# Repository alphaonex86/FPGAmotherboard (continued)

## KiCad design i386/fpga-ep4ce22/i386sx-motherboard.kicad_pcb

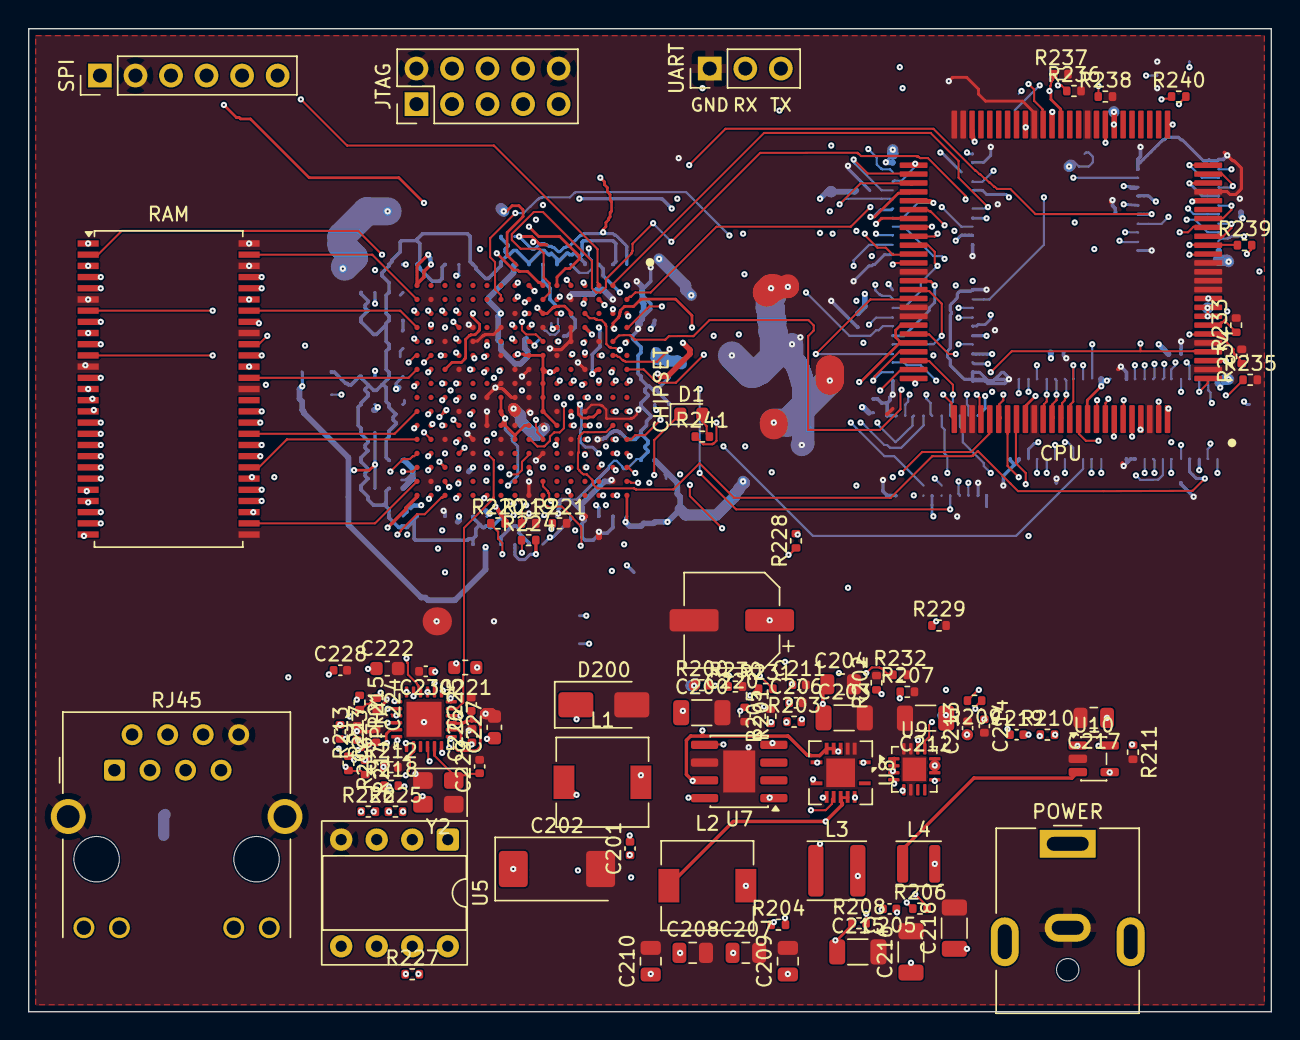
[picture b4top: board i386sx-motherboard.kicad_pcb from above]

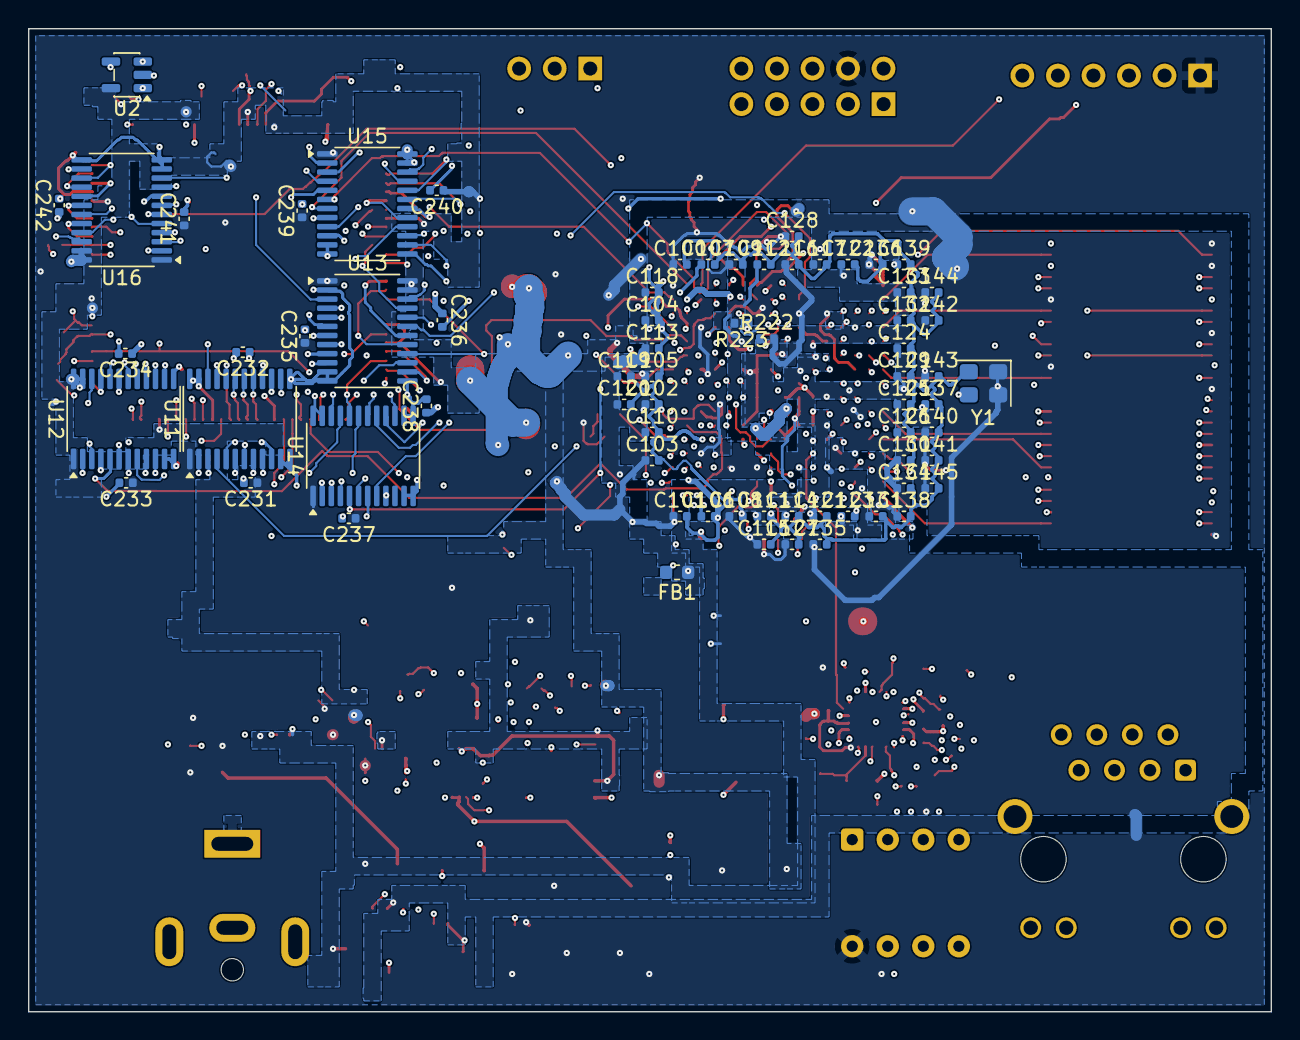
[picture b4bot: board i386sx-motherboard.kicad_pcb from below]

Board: 6 copper layers, 88.8 x 70.2 mm, 161 parts (69 on the bottom side), 213 nets.

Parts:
C100, C101, C102, C103, C104, C105, C106, C107, C108, C109, C110, C111, C112, C113, C114, C115, C116, C117, C118, C119, C120, C121, C122, C123, C124, C125, C126, C127, C128, C129, C130, C131, C132, C133, C134, C135, C136, C137, C138, C139, C140, C141, C142, C143, C144, C145: 100nF; C_0402_1005Metric
C200, C203, C212, C215, C216, C218: 22uF 25V X5R; C_1206_3216Metric
C201, C206: 10nF 50V X7R; C_0402_1005Metric
C202: 220uF 10V ESR<=40mR; CP_EIA-7343-31_Kemet-D
C204: 4.7uF 25V X7R; C_0805_2012Metric
C205, C213, C223, C224, C225, C228, C231, C232, C233, C234, C235, C236, C237, C238, C239, C240, C241, C242: 100nF 16V X7R; C_0402_1005Metric
C207, C208, C209, C210: 47uF 6.3V X5R; C_0805_2012Metric
C211: 8.2nF 50V X7R; C_0402_1005Metric
C214: 3.3nF 50V X7R; C_0402_1005Metric
C217: 10uF 16V X5R; C_0805_2012Metric
C219: 6.8pF 50V C0G; C_0402_1005Metric
C220: 100uF 25V; CP_Elec_6.3x7.7
C221: 600R@100MHz bead; L_0603_1608Metric
C222: 10uF 10V X5R; C_0603_1608Metric
C226: 470pF 50V C0G; C_0402_1005Metric
C227: 1uF 16V X7R; C_0603_1608Metric
C229, C230: 15pF 50V C0G; C_0402_1005Metric
D1: red LED KT-0603R; LED_0603_1608Metric
D200: B340A 40V 3A; D_SMA
FB1: 600R@100MHz bead; L_0603_1608Metric
J1: HR911105A; RJ45_Hanrun_HR911105A_Horizontal
J2: PJ-063AH 12V; BarrelJack_CUI_PJ-063AH_Horizontal
J3: JTAG; PinHeader_2x05_P2.54mm_Vertical
J4: SPI ISP; PinHeader_1x06_P2.54mm_Vertical
J5: UART; PinHeader_1x03_P2.54mm_Vertical
L1: 10uH ETQP4M100YFN; L_6.3x6.3_H3
L2: 2.2uH SRN6045TA-2R2Y; L_6.3x6.3_H3
L3: 2.2uH SLW4020P2R2MST; L_APV_ANR4020
L4: 1.0uH VLS3012HBX-1R0M; L_APV_ANR3012
R200: 30.9k 1%; R_0402_1005Metric
R201, R205, R207, R213, R222, R223, R224, R226, R227, R228, R229: 10k 1%; R_0402_1005Metric
R202, R208, R209, R211: 100k 1%; R_0402_1005Metric
R203: 1.69k 1%; R_0402_1005Metric
R204: 31.6k 1%; R_0402_1005Metric
R206: 4.99k 1%; R_0402_1005Metric
R210, R231: 316k 1%; R_0402_1005Metric
R212: 12.1k 1%; R_0402_1005Metric
R214, R215, R216, R217: 49.9 1%; R_0402_1005Metric
R218: 500R 1%; R_0402_1005Metric
R219, R220, R221: 0R; R_0402_1005Metric
R225: 24.9R 1%; R_0402_1005Metric
R230, R233, R234, R235, R236, R237, R238: 1k 1%; R_0402_1005Metric
R232: 46.4k 1%; R_0402_1005Metric
R239, R240: 21.5k 1%; R_0402_1005Metric
R241: 330R 1%; R_0402_1005Metric
U1: NG80386SX-20; Intel_PQFP-100_19.05x19.05mm_P0.635mm
U2: SN74AHCT1G125DBVR; SOT-23-5
U3: EP4CE22F17C8N; Altera_FBGA-256_F256_17x17mm_Layout16x16_P1.0mm
U4: W9825G6KH-6I; TSOP-II-54_22.2x10.16mm_P0.8mm
U5: W25Q64FVDAIG (DIP-8, socketed); DIP-8_W7.62mm_Socket
U6: LAN8720A-CP-TR; QFN-24-1EP_4x4mm_P0.5mm_EP2.5x2.5mm
U7: TPS5430DDAR 12->5V; SOIC-8-1EP_3.9x4.9mm_P1.27mm_EP2.29x3mm
U8: TPS54620RGYR 12->3V3; Texas_S-PVQFN-N14
U9: TPS62130RGTR VCCINT; VQFN-16-1EP_3x3mm_P0.5mm_EP1.68x1.68mm
U10: TLV62569DBVR VCCAUX; SOT-23-5
U11, U12, U13, U14, U15, U16: SN74LVC8T245PWR; TSSOP-24_4.4x7.8mm_P0.65mm
Y1: 25MHz XO; Oscillator_SMD_Abracon_ASE-4Pin_3.2x2.5mm
Y2: 25MHz; Crystal_SMD_3225-4Pin_3.2x2.5mm

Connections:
+3V3: C100.1, C101.1, C102.1, C103.1, C104.1, C105.1, C108.1, C109.1, C115.1, C116.1, C127.1, C128.1, C135.1, C136.1, C140.1, C141.1, C142.1, C143.1, C144.1, C145.1, C207.1, C208.1, C209.1, C210.1, C212.1, C213.1, C217.1, C221.1, C225.1, C231.1, C233.1, C235.1, C237.1, C239.1, C241.1, J3.4, J4.1, L2.2, R204.1, R209.1, R222.2, R223.2, R224.2, R226.2, R227.2, R228.2, R241.1, U3.A1 (VCCIO8), U3.A16 (VCCIO7), U3.C4 (VCCIO8), U3.C7 (VCCIO8), U3.C10 (VCCIO7), U3.C13 (VCCIO7), U3.E3 (VCCIO1), U3.E14 (VCCIO6), U3.G3 (VCCIO1), U3.G14 (VCCIO6), U3.K3 (VCCIO2), U3.K14 (VCCIO5), U3.M3 (VCCIO2), U3.M14 (VCCIO5), U3.P4 (VCCIO3), U3.P7 (VCCIO3), U3.P10 (VCCIO4), U3.P13 (VCCIO4), U3.T1 (VCCIO3), U3.T16 (VCCIO4), U4.1, U4.3, U4.9, U4.14, U4.27, U4.43, U4.49, U5.8, U6.9, U9.10, U9.11, U9.12, U10.1, U10.4, U11.1, U12.1, U13.1, U14.1, U15.1, U16.1, Y1.1, Y1.4
+5V: C202.1, C232.1, C234.1, C236.1, C238.1, C240.1, C242.1, L1.2, R200.1, R239.2, R240.2, U1.8, U1.9, U1.10, U1.21, U1.32, U1.39, U1.42, U1.48, U1.57, U1.69, U1.71, U1.84, U1.91, U1.97, U2.5, U11.23, U11.24, U12.23, U12.24, U13.23, U13.24, U14.23, U14.24, U15.23, U15.24, U16.23, U16.24
+12V: C200.1, C203.1, C204.1, C220.1, J2.1, R231.1, U7.7, U8.4, U8.5, U8.6
GND: C100.2, C101.2, C102.2, C103.2, C104.2, C105.2, C106.2, C107.2, C108.2, C109.2, C110.2, C111.2, C112.2, C113.2, C114.2, C115.2, C116.2, C117.2, C118.2, C119.2, C120.2, C121.2, C122.2, C123.2, C124.2, C125.2, C126.2, C127.2, C128.2, C129.2, C130.2, C131.2, C132.2, C133.2, C134.2, C135.2, C136.2, C137.2, C138.2, C139.2, C140.2, C141.2, C142.2, C143.2, C144.2, C145.2, C200.2, C202.2, C203.2, C204.2, C206.2, C207.2, C208.2, C209.2, C210.2, C211.2, C212.2, C213.2, C214.2, C215.2, C216.2, C217.2, C218.2, C220.2, C222.2, C223.2, C224.2, C225.2, C226.2, C227.2, C228.2, C229.2, C230.2, C231.2, C232.2, C233.2, C234.2, C235.2, C236.2, C237.2, C238.2, C239.2, C240.2, C241.2, C242.2, D200.2, J1.8, J1.SH, J2.2, J3.2, J3.10, J4.2, J5.1, R201.2, R202.2, R205.2, R207.2, R211.2, R212.2, R213.2, R219.2, R221.2, R229.2, R230.2, R232.2, R233.2, R234.2, R235.2, R236.2, R237.2, R238.2, U1.2, U1.5, U1.11, U1.12, U1.13, U1.14, U1.22, U1.35, U1.41, U1.49, U1.50, U1.63, U1.67, U1.68, U1.77, U1.78, U1.85, U1.98, U2.1, U2.3, U3.B2 (GND), U3.B15 (GND), U3.C5 (GND), U3.C12 (GND), U3.D7 (GND), U3.D10 (GND), U3.E2 (GND), U3.E4 (GND), U3.E5 (GNDA3), U3.E12 (GNDA2), U3.E13 (GND), U3.F6 (GND), U3.F10 (GND), U3.G4 (GND), U3.G11 (GND), U3.G13 (GND), U3.H7 (GND), U3.H8 (GND), U3.H9 (GND), U3.H10 (GND), U3.H15 (GND), U3.H16 (GND), U3.J3 (nCE), U3.J7 (GND), U3.J8 (GND), U3.J9 (GND), U3.J10 (GND), U3.J11 (GND), U3.K4 (GND), U3.K6 (GND), U3.K8 (GND), U3.K12 (GND), U3.K13 (GND), U3.L9 (GND), U3.L10 (GND), U3.L11 (GND), U3.M4 (GND), U3.M5 (GNDA1), U3.M12 (GNDA4), U3.M13 (GND), U3.N7 (GND), U3.N10 (GND), U3.P5 (GND), U3.P12 (GND), U3.R2 (GND), U3.R15 (GND), U4.6, U4.12, U4.28, U4.41, U4.46, U4.52, U4.54, U5.4, U6.25, U7.6, U7.9, U8.2, U8.3, U8.15, U9.6, U9.15, U9.16, U9.17, U10.2, U11.11, U11.12, U11.13, U12.11, U12.12, U12.13, U13.2, U13.11, U13.12, U13.13, U14.2, U14.11, U14.12, U14.13, U14.14, U15.2, U15.11, U15.12, U15.13, U16.2, U16.11, U16.12, U16.13, Y1.2, Y2.2, Y2.4
VCCA_PLL: C111.1, C112.1, C131.1, C132.1, C218.1, C219.1, L4.2, R210.1, R220.2, U3.F5 (VCCA3), U3.F12 (VCCA2), U3.L5 (VCCA1), U3.L12 (VCCA4)
VCCD_PLL: C106.1, C107.1, C138.1, C139.1, FB1.2, U3.D4 (VCCD_PLL3), U3.D13 (VCCD_PLL2), U3.N4 (VCCD_PLL1), U3.N13 (VCCD_PLL4)
VCCINT: C110.1, C113.1, C114.1, C117.1, C118.1, C119.1, C120.1, C121.1, C122.1, C123.1, C124.1, C125.1, C126.1, C129.1, C130.1, C133.1, C134.1, C137.1, C215.1, C216.1, FB1.1, L3.2, R206.1, R208.1, U3.F7 (VCCINT), U3.F11 (VCCINT), U3.G6 (VCCINT), U3.G7 (VCCINT), U3.G8 (VCCINT), U3.G9 (VCCINT), U3.G10 (VCCINT), U3.H6 (VCCINT), U3.H11 (VCCINT), U3.J6 (VCCINT), U3.J12 (VCCINT), U3.K7 (VCCINT), U3.K9 (VCCINT), U3.K10 (VCCINT), U3.K11 (VCCINT), U3.L6 (VCCINT), U3.M9 (VCCINT), U3.M11 (VCCINT), U9.14
clk25: U3.T8 (CLK14), Y1.3
cpu_a[1]: U1.18, U16.19
cpu_a[2]: U1.51, U15.21
cpu_a[3]: U1.52, U15.20
cpu_a[4]: U1.53, U15.19
cpu_a[5]: U1.54, U15.18
cpu_a[6]: U1.55, U15.17
cpu_a[7]: U1.56, U15.16
cpu_a[8]: U1.58, U15.15
cpu_a[9]: U1.59, U15.14
cpu_a[10]: U1.60, U13.21
cpu_a[11]: U1.61, U13.20
cpu_a[12]: U1.62, U13.19
cpu_a[13]: U1.64, U13.18
cpu_a[14]: U1.65, U13.17
cpu_a[15]: U1.66, U13.16
cpu_a[16]: U1.70, U13.15
cpu_a[17]: U1.72, U13.14
cpu_a[18]: U1.73, U14.20
cpu_a[19]: U1.74, U14.19
cpu_a[20]: U1.75, U14.18
cpu_a[21]: U1.76, U14.15
cpu_a[22]: U1.79, U14.16
cpu_a[23]: U1.80, U14.17
cpu_ads_n: R239.1, U1.16, U16.21
cpu_bhe_n: U1.19, U16.18
cpu_ble_n: U1.17, U16.20
cpu_clk2: U1.15, U2.4
cpu_d[0]: U1.1, U12.21
cpu_d[1]: U1.100, U12.20
cpu_d[2]: U1.99, U12.19
cpu_d[3]: U1.96, U12.18
cpu_d[4]: U1.95, U12.17
cpu_d[5]: U1.94, U12.16
cpu_d[6]: U1.93, U12.15
cpu_d[7]: U1.92, U12.14
cpu_d[8]: U1.90, U11.21
cpu_d[9]: U1.89, U11.20
cpu_d[10]: U1.88, U11.19
cpu_d[11]: U1.87, U11.18
cpu_d[12]: U1.86, U11.17
cpu_d[13]: U1.83, U11.16
cpu_d[14]: U1.82, U11.15
cpu_d[15]: U1.81, U11.14
cpu_dc_n: U1.24, U16.16
cpu_hlda: U1.3, U14.21
cpu_hold: R235.1, U1.4, U3.E8 (IO)
cpu_intr: R236.1, U1.40, U3.D6 (IO)
cpu_lock_n: R240.1, U1.26, U16.14
cpu_mio_n: U1.23, U16.17
cpu_na_n: R234.1, U1.6, U3.C8 (IO)
cpu_nmi: R237.1, U1.38, U3.G1 (IO)
cpu_pwr_en: R230.1, U3.G16 (IO), U7.5
cpu_ready_n: R233.1, U1.7, U3.A7 (IO)
cpu_reset: R238.1, U1.33, U3.B7 (IO)
cpu_wr_n: U1.25, U16.15
eth_mdc: U3.N15 (IO), U6.13
eth_mdi_rxn: J1.6, R217.1, U6.22
eth_mdi_rxp: J1.3, R216.1, U6.23
eth_mdi_txn: J1.2, R215.1, U6.20
eth_mdi_txp: J1.1, R214.1, U6.21
eth_mdio: U3.N16 (IO), U6.12
eth_nintsel: R213.1, U6.2
eth_rbias: R212.1, U6.24
eth_ref_clk: U3.E16 (CLK5), U6.14
eth_rmii_crs_dv: U3.L13 (IO), U6.11
eth_rmii_rx_er: U3.L14 (IO), U6.10
eth_rmii_rxd[0]: U3.L15 (IO), U6.8
eth_rmii_rxd[1]: U3.L16 (IO), U6.7
eth_rmii_tx_en: U3.P16 (IO), U6.16
eth_rmii_txd[0]: U3.P15 (IO), U6.17
eth_rmii_txd[1]: U3.R16 (IO), U6.18
eth_rst_n: U3.N14 (IO), U6.15
eth_vdda: C221.2, C222.1, C223.1, C224.1, C228.1, J1.4, J1.5, R214.2, R215.2, R216.2, R217.2, U6.1, U6.19
eth_vddcr: C226.1, C227.1, U6.6
eth_xtal1: C229.1, U6.5, Y2.1
eth_xtal2: C230.1, R218.1, Y2.3
eth_xtal2_drv: R218.2, U6.4
fpga_a[1]: U3.D5 (IO), U16.5
fpga_a[2]: U3.F1 (IO), U15.3
fpga_a[3]: U3.E1 (CLK1), U15.4
fpga_a[4]: U3.D1 (IO), U15.5
fpga_a[5]: U3.G2 (IO), U15.6
fpga_a[6]: U3.B1 (IO), U15.7
fpga_a[7]: U3.C2 (IO), U15.8
fpga_a[8]: U3.A2 (IO), U15.9
fpga_a[9]: U3.K2 (IO), U15.10
fpga_a[10]: U3.B3 (IO), U13.3
fpga_a[11]: U3.B8 (CLK11), U13.4
fpga_a[12]: U3.A8 (CLK10), U13.5
fpga_a[13]: U3.E6 (IO), U13.6
fpga_a[14]: U3.B4 (IO), U13.7
fpga_a[15]: U3.A4 (IO), U13.8
fpga_a[16]: U3.B5 (IO), U13.9
fpga_a[17]: U3.A5 (IO), U13.10
fpga_a[18]: U3.C9 (IO), U14.4
fpga_a[19]: U3.D9 (IO), U14.5
fpga_a[20]: U3.E9 (IO), U14.6
fpga_a[21]: U3.B16 (IO), U14.9
fpga_a[22]: U3.B10 (IO), U14.8
fpga_a[23]: U3.F9 (IO), U14.7
fpga_ads_n: U3.D8 (IO), U16.3
fpga_bhe_n: U3.G5 (IO), U16.6
fpga_ble_n: U3.C6 (IO), U16.4
fpga_clk2: U2.2, U3.F8 (IO)
fpga_conf_done: R224.1, U3.H14 (CONF_DONE)
fpga_d[0]: U3.A10 (IO), U12.3
fpga_d[1]: U3.E10 (IO), U12.4
fpga_d[2]: U3.B11 (IO), U12.5
fpga_d[3]: U3.A11 (IO), U12.6
fpga_d[4]: U3.C11 (IO), U12.7
fpga_d[5]: U3.D11 (IO), U12.8
fpga_d[6]: U3.E11 (IO), U12.9
fpga_d[7]: U3.A12 (IO), U12.10
fpga_d[8]: U3.A14 (IO), U11.3
fpga_d[9]: U3.B12 (IO), U11.4
fpga_d[10]: U3.D12 (IO), U11.5
fpga_d[11]: U3.A13 (IO), U11.6
fpga_d[12]: U3.B13 (IO), U11.7
fpga_d[13]: U3.A15 (IO), U11.8
fpga_d[14]: U3.C14 (IO), U11.9
fpga_d[15]: U3.D14 (IO), U11.10
fpga_dc_n: U3.D3 (IO), U16.8
fpga_hlda: U3.B14 (IO), U14.3
fpga_lock_n: U3.F2 (IO), U16.10
fpga_mio_n: U3.A3 (IO), U16.7
fpga_msel0: R219.1, U3.H13 (MSEL0)
fpga_msel1: R220.1, U3.H12 (MSEL1)
fpga_msel2: R221.1, U3.G12 (MSEL2)
fpga_nconfig: R222.1, U3.H5 (nCONFIG)
fpga_nstatus: R223.1, U3.F4 (nSTATUS)
fpga_wr_n: U3.F3 (IO), U16.9
fpga_xlat_dir: R229.1, U3.C16 (IO), U11.2, U12.2
fpga_xlat_oe_n: R228.1, U3.B6 (IO), U11.22, U12.22, U13.22, U14.22, U15.22, U16.22
jtag_tck: J3.1, U3.H3 (TCK)
jtag_tdi: J3.9, U3.H4 (TDI)
jtag_tdo: J3.3, U3.J4 (TDO)
jtag_tms: J3.5, U3.J5 (TMS)
led_a: D1.2, R241.2
led_n: D1.1, U3.G15 (IO)
sdram_a[0]: U3.N11 (IO), U4.23
sdram_a[1]: U3.R12 (IO), U4.24
sdram_a[2]: U3.T13 (IO), U4.25
sdram_a[3]: U3.T14 (IO), U4.26
sdram_a[4]: U3.T15 (IO), U4.29
sdram_a[5]: U3.P14 (IO), U4.30
sdram_a[6]: U3.R14 (IO), U4.31
sdram_a[7]: U3.R13 (IO), U4.32
sdram_a[8]: U3.N12 (IO), U4.33
sdram_a[9]: U3.T12 (IO), U4.34
sdram_a[10]: U3.R11 (IO), U4.22
sdram_a[11]: U3.P11 (IO), U4.35
sdram_a[12]: U3.M10 (IO), U4.36
sdram_ba[0]: U3.R10 (IO), U4.20
sdram_ba[1]: U3.T11 (IO), U4.21
sdram_cas_n: U3.L7 (IO), U4.17
sdram_cke: U3.T10 (IO), U4.37
sdram_clk: U3.P9 (IO), U4.38
sdram_cs_n: U3.N9 (IO), U4.19
sdram_dq[0]: U3.P3 (IO), U4.2
sdram_dq[1]: U3.T3 (IO), U4.4
sdram_dq[2]: U3.R4 (IO), U4.5
sdram_dq[3]: U3.R5 (IO), U4.7
sdram_dq[4]: U3.T5 (IO), U4.8
sdram_dq[5]: U3.N6 (IO), U4.10
sdram_dq[6]: U3.T6 (IO), U4.11
sdram_dq[7]: U3.R6 (IO), U4.13
sdram_dq[8]: U3.T7 (IO), U4.42
sdram_dq[9]: U3.P6 (IO), U4.44
sdram_dq[10]: U3.M6 (IO), U4.45
sdram_dq[11]: U3.N5 (IO), U4.47
sdram_dq[12]: U3.T4 (IO), U4.48
sdram_dq[13]: U3.R3 (IO), U4.50
sdram_dq[14]: U3.N3 (IO), U4.51
sdram_dq[15]: U3.T2 (IO), U4.53
sdram_dqm[0]: U3.R7 (IO), U4.15
sdram_dqm[1]: U3.N8 (IO), U4.39
sdram_ras_n: U3.P8 (IO), U4.18
sdram_we_n: U3.M7 (IO), U4.16
spi_clk: J4.4, U3.H1 (DCLK), U5.6
spi_cs_n: J4.3, U3.D2 (IO), U5.1
spi_io2: R226.1, U5.3
spi_io3: R227.1, U5.7
spi_miso: J4.5, R225.2, U3.H2 (IO)
spi_miso_flash: R225.1, U5.2
spi_mosi: J4.6, U3.C1 (IO), U5.5
sw_3v3: C205.2, L2.1, U8.11, U8.12
sw_5v0: C201.2, D200.1, L1.1, U7.8
sw_vcca: L4.1, U10.3
sw_vccint: L3.1, U9.1, U9.2, U9.3
u7_boot: C201.1, U7.1
u7_fb: R200.2, R201.1, U7.4
u8_boot: C205.1, U8.13
u8_comp: R203.1, U8.8
u8_compz: C211.1, R203.2
u8_en: R231.2, R232.1, U8.10
u8_fb: R204.2, R205.1, U8.7
u8_rt: R202.1, U8.1
u8_ss: C206.1, U8.9
u9_en: R209.2, U9.13
u9_fb: R206.2, R207.1, U9.5
u9_pg: R208.2, U9.4
u9_ss: C214.1, U9.9
u10_fb: C219.2, R210.2, R211.1, U10.5
uart_rx: J5.2, U3.J1 (IO)
uart_tx: J5.3, U3.J2 (IO)

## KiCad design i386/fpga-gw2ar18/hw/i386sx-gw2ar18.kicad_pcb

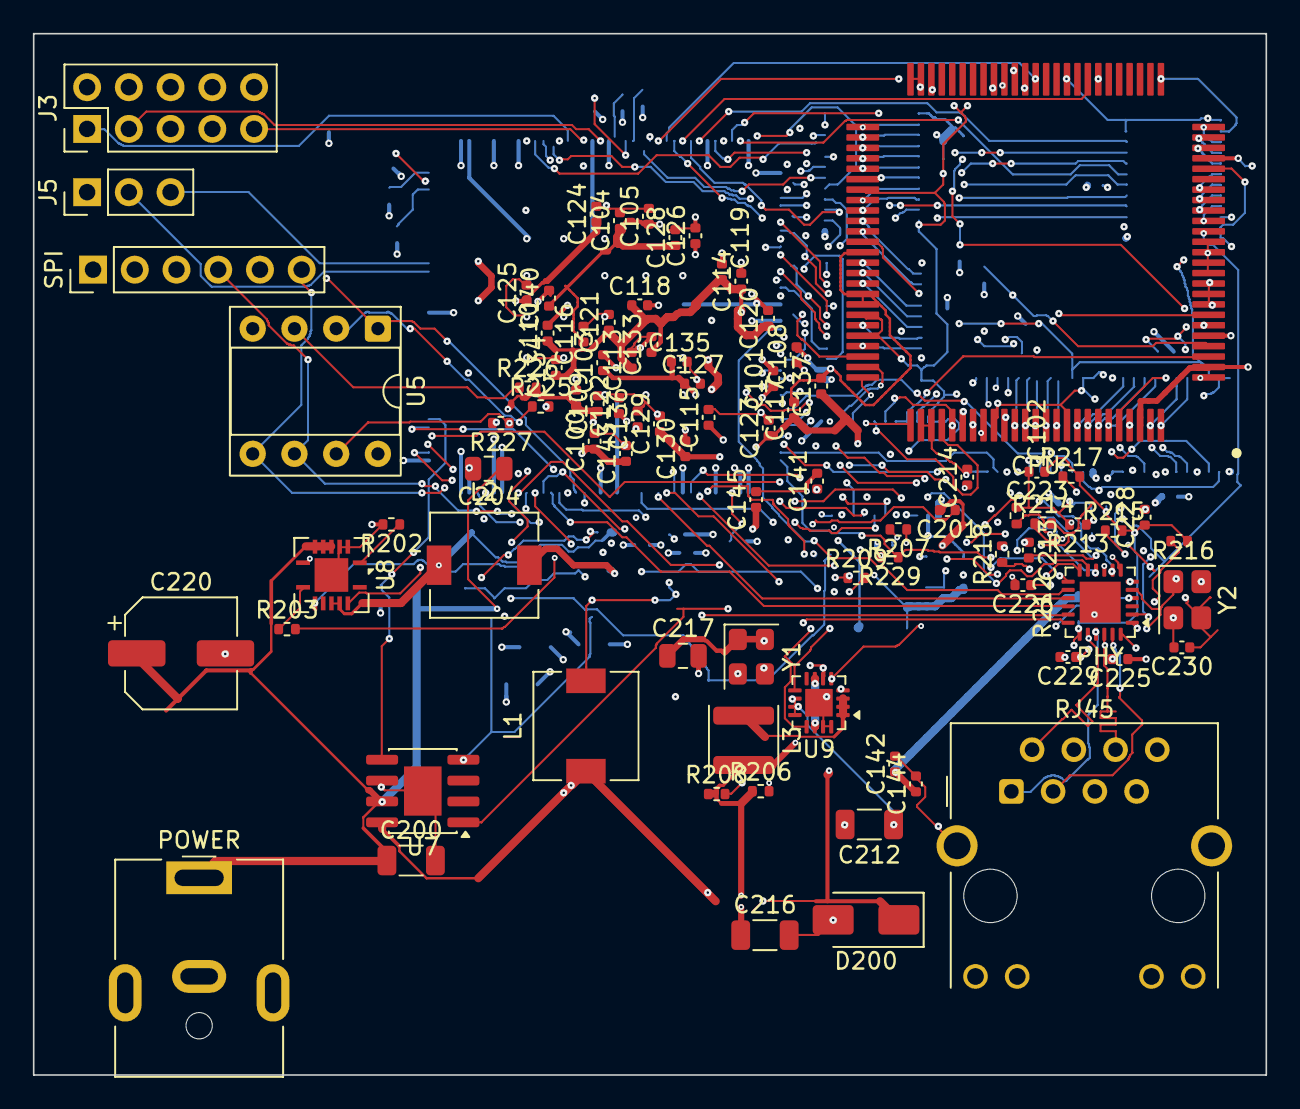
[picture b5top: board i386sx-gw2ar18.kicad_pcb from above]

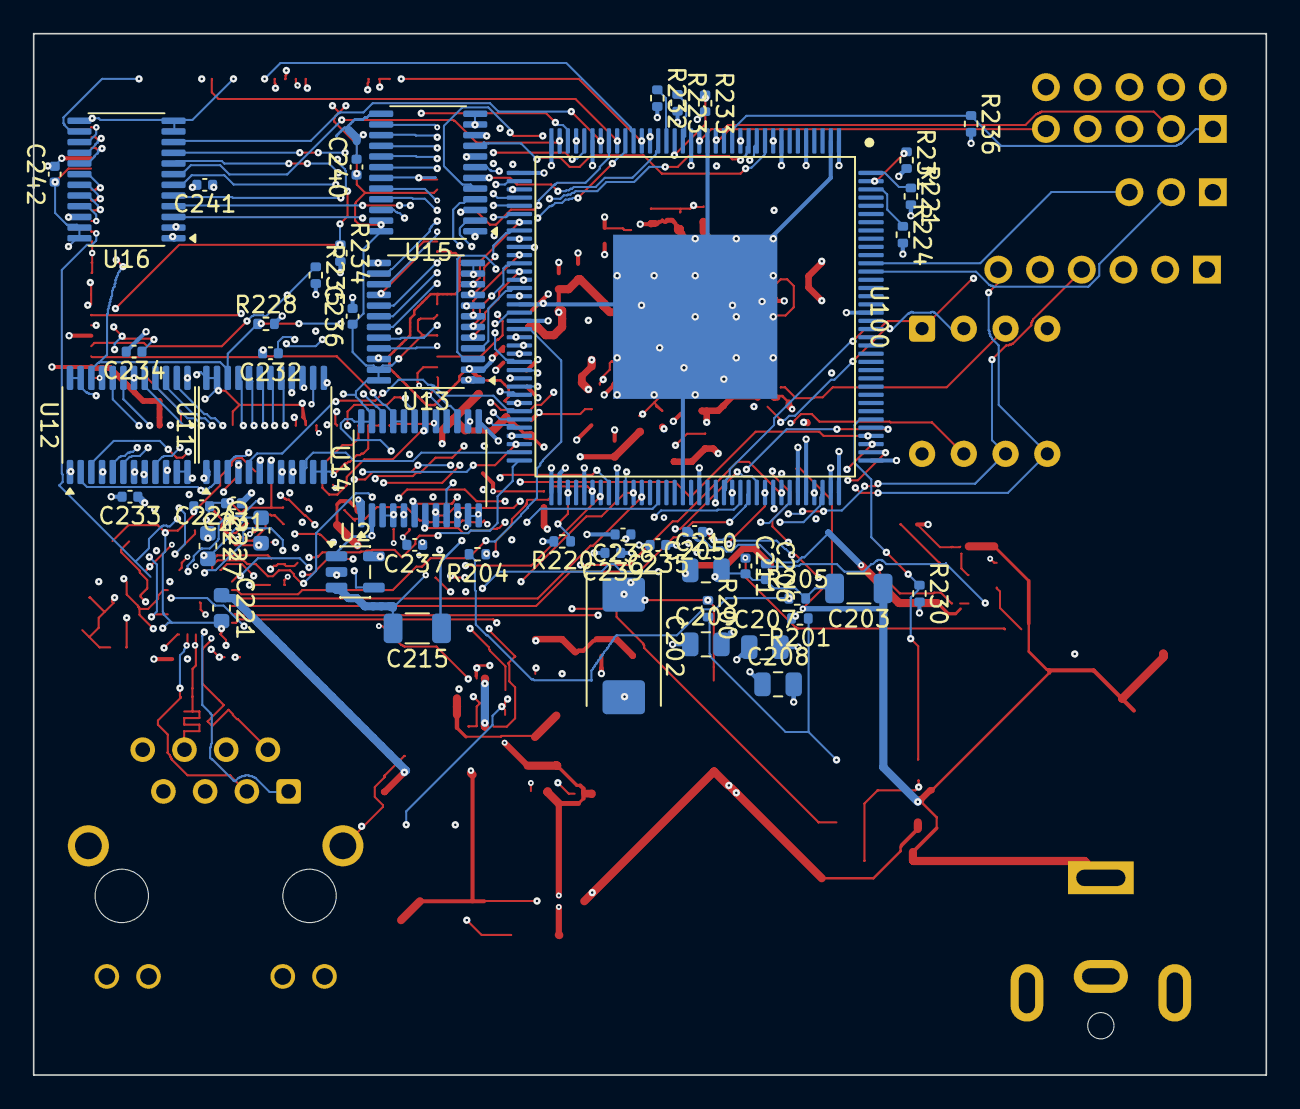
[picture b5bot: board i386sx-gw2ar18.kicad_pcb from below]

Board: 6 copper layers, 75.0 x 63.4 mm, 137 parts (50 on the bottom side), 168 nets.

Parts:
C100, C101, C102, C103, C104, C105, C108, C109, C110, C113, C114, C115, C116, C117, C118, C119, C120, C121, C122, C123, C124, C125, C126, C127, C128, C129, C130, C133, C134, C135, C136, C137, C140, C141, C142, C143, C144, C145: 100nF; C_0402_1005Metric
C200, C203, C212, C215, C216: 22uF 25V X5R; C_1206_3216Metric
C201, C206: 10nF 50V X7R; C_0402_1005Metric
C202: 220uF 10V ESR<=40mR; CP_EIA-7343-31_Kemet-D
C204: 4.7uF 25V X7R; C_0805_2012Metric
C205, C213, C223, C224, C225, C228, C231, C232, C233, C234, C235, C236, C237, C238, C239, C240, C241, C242: 100nF 16V X7R; C_0402_1005Metric
C207, C208, C209, C210: 47uF 6.3V X5R; C_0805_2012Metric
C211: 8.2nF 50V X7R; C_0402_1005Metric
C214: 3.3nF 50V X7R; C_0402_1005Metric
C217: 10uF 16V X5R; C_0805_2012Metric
C220: 100uF 25V; CP_Elec_6.3x7.7
C221: 600R@100MHz bead; L_0603_1608Metric
C222: 10uF 10V X5R; C_0603_1608Metric
C226: 470pF 50V C0G; C_0402_1005Metric
C227: 1uF 16V X7R; C_0603_1608Metric
C229, C230: 15pF 50V C0G; C_0402_1005Metric
D200: B340A 40V 3A; D_SMA
J1: HR911105A; RJ45_Hanrun_HR911105A_Horizontal
J2: PJ-063AH 12V; BarrelJack_CUI_PJ-063AH_Horizontal
J3: JTAG; PinHeader_2x05_P2.54mm_Vertical
J4: SPI ISP; PinHeader_1x06_P2.54mm_Vertical
J5: UART; PinHeader_1x03_P2.54mm_Vertical
L1: 10uH ETQP4M100YFN; L_6.3x6.3_H3
L2: 2.2uH SRN6045TA-2R2Y; L_6.3x6.3_H3
L3: 2.2uH SLW4020P2R2MST; L_APV_ANR4020
R200: 30.9k 1%; R_0402_1005Metric
R201, R205, R207, R213, R220, R223, R226, R227, R228, R229: 10k 1%; R_0402_1005Metric
R202, R208, R209: 100k 1%; R_0402_1005Metric
R203: 1.69k 1%; R_0402_1005Metric
R204: 31.6k 1%; R_0402_1005Metric
R206: 2.49k 1%; R_0402_1005Metric
R212: 12.1k 1%; R_0402_1005Metric
R214, R215, R216, R217: 49.9 1%; R_0402_1005Metric
R218: 500R 1%; R_0402_1005Metric
R221, R224, R230, R231, R234, R235: 1k 1%; R_0402_1005Metric
R225: 24.9R 1%; R_0402_1005Metric
R232, R233, R236: 4.7k 1%; R_0402_1005Metric
U1: NG80386SX-20; Intel_PQFP-100_19.05x19.05mm_P0.635mm
U2: SN74AHCT1G125DBVR; SOT-23-5
U5: W25Q64FVDAIG (DIP-8, socketed); DIP-8_W7.62mm_Socket
U6: LAN8720A-CP-TR; QFN-24-1EP_4x4mm_P0.5mm_EP2.5x2.5mm
U7: TPS5430DDAR 12->5V; SOIC-8-1EP_3.9x4.9mm_P1.27mm_EP2.29x3mm
U8: TPS54620RGYR 12->3V3; Texas_S-PVQFN-N14
U9: TPS62130RGTR VCCINT; VQFN-16-1EP_3x3mm_P0.5mm_EP1.68x1.68mm
U11, U12, U13, U14, U15, U16: SN74LVC8T245PWR; TSSOP-24_4.4x7.8mm_P0.65mm
U100: GW2AR-LV18EQ144C8/I7; GW2AR-LV18EQ144C8_I7
Y1: 25MHz XO; Oscillator_SMD_Abracon_ASE-4Pin_3.2x2.5mm
Y2: 25MHz; Crystal_SMD_3225-4Pin_3.2x2.5mm

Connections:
+3V3: C100.1, C101.1, C102.1, C103.1, C104.1, C105.1, C108.1, C109.1, C115.1, C116.1, C127.1, C128.1, C135.1, C136.1, C140.1, C141.1, C142.1, C143.1, C144.1, C145.1, C207.1, C208.1, C209.1, C210.1, C217.1, C221.1, C225.1, C231.1, C233.1, C235.1, C237.1, C239.1, C241.1, J3.4, J4.1, L2.2, R204.1, R223.2, R226.2, R227.2, R228.2, R232.2, R233.2, U5.8, U6.9, U11.1, U12.1, U13.1, U14.1, U15.1, U16.1, U100.5, U100.19, U100.31, U100.37, U100.55, U100.77, U100.91, U100.103, U100.109, U100.127, Y1.1, Y1.4
+5V: C202.1, C212.1, C213.1, C232.1, C234.1, C236.1, C238.1, C240.1, C242.1, L1.2, R200.1, R209.1, U1.8, U1.9, U1.10, U1.21, U1.32, U1.39, U1.42, U1.48, U1.57, U1.69, U1.71, U1.84, U1.91, U1.97, U2.5, U9.10, U9.11, U9.12, U11.23, U11.24, U12.23, U12.24, U13.23, U13.24, U14.23, U14.24, U15.23, U15.24, U16.23, U16.24
+12V: C200.1, C203.1, C204.1, C220.1, J2.1, U7.7, U8.4, U8.5, U8.6
GND: C100.2, C101.2, C102.2, C103.2, C104.2, C105.2, C108.2, C109.2, C110.2, C113.2, C114.2, C115.2, C116.2, C117.2, C118.2, C119.2, C120.2, C121.2, C122.2, C123.2, C124.2, C125.2, C126.2, C127.2, C128.2, C129.2, C130.2, C133.2, C134.2, C135.2, C136.2, C137.2, C140.2, C141.2, C142.2, C143.2, C144.2, C145.2, C200.2, C202.2, C203.2, C204.2, C206.2, C207.2, C208.2, C209.2, C210.2, C211.2, C212.2, C213.2, C214.2, C215.2, C216.2, C217.2, C220.2, C222.2, C223.2, C224.2, C225.2, C226.2, C227.2, C228.2, C229.2, C230.2, C231.2, C232.2, C233.2, C234.2, C235.2, C236.2, C237.2, C238.2, C239.2, C240.2, C241.2, C242.2, D200.2, J1.8, J1.SH, J2.2, J3.2, J3.10, J4.2, J5.1, R201.2, R202.2, R205.2, R207.2, R212.2, R213.2, R220.2, R221.2, R224.2, R229.2, R230.2, R231.2, R234.2, R235.2, R236.2, U1.2, U1.5, U1.11, U1.12, U1.13, U1.14, U1.22, U1.35, U1.41, U1.49, U1.50, U1.63, U1.67, U1.68, U1.77, U1.78, U1.85, U1.98, U2.1, U2.3, U5.4, U6.25, U7.6, U7.9, U8.2, U8.3, U8.15, U9.6, U9.15, U9.16, U9.17, U11.11, U11.12, U11.13, U12.11, U12.12, U12.13, U13.2, U13.11, U13.12, U13.13, U14.2, U14.11, U14.12, U14.13, U15.2, U15.11, U15.12, U15.13, U16.2, U16.11, U16.12, U16.13, U100.2, U100.17, U100.53, U100.74, U100.89, U100.107, U100.145, Y1.2, Y2.2, Y2.4
VCCINT: C110.1, C113.1, C114.1, C117.1, C118.1, C119.1, C120.1, C121.1, C122.1, C123.1, C124.1, C125.1, C126.1, C129.1, C130.1, C133.1, C134.1, C137.1, C215.1, C216.1, L3.2, R206.1, R208.1, U9.7, U9.14, U100.1, U100.8, U100.36, U100.73, U100.81, U100.104, U100.108
clk25: U100.98, Y1.3
cpu_a[1]: U1.18, U16.19
cpu_a[2]: U1.51, U15.14
cpu_a[3]: U1.52, U15.15
cpu_a[4]: U1.53, U15.16
cpu_a[5]: U1.54, U15.17
cpu_a[6]: U1.55, U15.18
cpu_a[7]: U1.56, U15.19
cpu_a[8]: U1.58, U15.20
cpu_a[9]: U1.59, U15.21
cpu_a[10]: U1.60, U13.14
cpu_a[11]: U1.61, U13.15
cpu_a[12]: U1.62, U13.16
cpu_a[13]: U1.64, U13.17
cpu_a[14]: U1.65, U13.18
cpu_a[15]: U1.66, U13.19
cpu_a[16]: U1.70, U13.20
cpu_a[17]: U1.72, U13.21
cpu_a[18]: U1.73, U14.14
cpu_a[19]: U1.74, U14.15
cpu_a[20]: U1.75, U14.16
cpu_a[21]: U1.76, U14.17
cpu_a[22]: U1.79, U14.18
cpu_a[23]: U1.80, U14.19
cpu_ads_n: U1.16, U16.21
cpu_bhe_n: U1.19, U16.18
cpu_ble_n: U1.17, U16.20
cpu_clk2: U1.15, U2.4
cpu_d[0]: U1.1, U12.21
cpu_d[1]: U1.100, U12.20
cpu_d[2]: U1.99, U12.19
cpu_d[3]: U1.96, U12.18
cpu_d[4]: U1.95, U12.17
cpu_d[5]: U1.94, U12.16
cpu_d[6]: U1.93, U12.15
cpu_d[7]: U1.92, U12.14
cpu_d[8]: U1.90, U11.21
cpu_d[9]: U1.89, U11.20
cpu_d[10]: U1.88, U11.19
cpu_d[11]: U1.87, U11.18
cpu_d[12]: U1.86, U11.17
cpu_d[13]: U1.83, U11.16
cpu_d[14]: U1.82, U11.15
cpu_d[15]: U1.81, U11.14
cpu_dc_n: U1.24, U16.16
cpu_hlda: U1.3, U14.20, U14.21
cpu_hold: R235.1, U1.4, U100.39
cpu_intr: U1.40, U100.25
cpu_lock_n: U1.26, U16.14
cpu_mio_n: U1.23, U16.17
cpu_na_n: R234.1, U1.6, U100.34
cpu_nmi: U1.38, U100.26
cpu_pwr_en: R230.1, U7.5, U100.114
cpu_ready_n: U1.7, U100.46
cpu_reset: U1.33, U100.28
cpu_wr_n: U1.25, U16.15
eth_mdc: U6.13, U100.83
eth_mdi_rxn: J1.6, R217.1, U6.22
eth_mdi_rxp: J1.3, R216.1, U6.23
eth_mdi_txn: J1.2, R215.1, U6.20
eth_mdi_txp: J1.1, R214.1, U6.21
eth_mdio: U6.12, U100.82
eth_nintsel: R213.1, U6.2
eth_rbias: R212.1, U6.24
eth_ref_clk: U6.14, U100.56
eth_rmii_crs_dv: U6.11, U100.80
eth_rmii_rx_er: U6.10, U100.79
eth_rmii_rxd[0]: U6.8, U100.78
eth_rmii_rxd[1]: U6.7, U100.86
eth_rmii_tx_en: U6.16, U100.97
eth_rmii_txd[0]: U6.17, U100.99
eth_rmii_txd[1]: U6.18, U100.101
eth_rst_n: U6.15, U100.84
eth_vdda: C221.2, C222.1, C223.1, C224.1, C228.1, J1.4, J1.5, R214.2, R215.2, R216.2, R217.2, U6.1, U6.19
eth_vddcr: C226.1, C227.1, U6.6
eth_xtal1: C229.1, U6.5, Y2.1
eth_xtal2: C230.1, R218.1, Y2.3
eth_xtal2_drv: R218.2, U6.4
fpga_a[1]: U16.5, U100.40
fpga_a[2]: U15.10, U100.9
fpga_a[3]: U15.9, U100.10
fpga_a[4]: U15.8, U100.11
fpga_a[5]: U15.7, U100.12
fpga_a[6]: U15.6, U100.23
fpga_a[7]: U15.5, U100.24
fpga_a[8]: U15.4, U100.27
fpga_a[9]: U15.3, U100.29
fpga_a[10]: U13.10, U100.43
fpga_a[11]: U13.9, U100.44
fpga_a[12]: U13.8, U100.45
fpga_a[13]: U13.7, U100.47
fpga_a[14]: U13.6, U100.48
fpga_a[15]: U13.5, U100.49
fpga_a[16]: U13.4, U100.51
fpga_a[17]: U13.3, U100.52
fpga_a[18]: U14.10, U100.113
fpga_a[19]: U14.9, U100.112
fpga_a[20]: U14.8, U100.111
fpga_a[21]: U14.7, U100.110
fpga_a[22]: U14.6, U100.105
fpga_a[23]: U14.5, U100.102
fpga_ads_n: U16.3, U100.42
fpga_bhe_n: U16.6, U100.38
fpga_ble_n: U16.4, U100.41
fpga_clk2: U2.2, U100.106
fpga_d[0]: U12.3, U100.54
fpga_d[1]: U12.4, U100.57
fpga_d[2]: U12.5, U100.58
fpga_d[3]: U12.6, U100.59
fpga_d[4]: U12.7, U100.60
fpga_d[5]: U12.8, U100.61
fpga_d[6]: U12.9, U100.62
fpga_d[7]: U12.10, U100.63
fpga_d[8]: U11.3, U100.64
fpga_d[9]: U11.4, U100.65
fpga_d[10]: U11.5, U100.66
fpga_d[11]: U11.6, U100.67
fpga_d[12]: U11.7, U100.68
fpga_d[13]: U11.8, U100.69
fpga_d[14]: U11.9, U100.70
fpga_d[15]: U11.10, U100.71
fpga_dc_n: U16.8, U100.33
fpga_done: R233.1, U100.21
fpga_extr: R220.1, U100.75
fpga_hlda: U14.3, U14.4, U100.100
fpga_lock_n: U16.10, U100.30
fpga_mio_n: U16.7, U100.35
fpga_mode0: R221.1, U100.144
fpga_mode1: R224.1, U100.142
fpga_mode2: R231.1, U100.143
fpga_ready: R232.1, U100.22
fpga_reconfig_n: R223.1, U100.20
fpga_wr_n: U16.9, U100.32
fpga_xlat_dir: R229.1, U11.2, U12.2, U100.72
fpga_xlat_oe_n: R228.1, U11.22, U12.22, U13.22, U14.22, U15.22, U16.22, U100.50
jtag_tck: J3.1, R236.1, U100.14
jtag_tdi: J3.9, U100.16
jtag_tdo: J3.3, U100.18
jtag_tms: J3.5, U100.13
spi_clk: J4.4, U5.6, U100.93
spi_cs_n: J4.3, U5.1, U100.94
spi_io2: R226.1, U5.3
spi_io3: R227.1, U5.7
spi_miso: J4.5, R225.2, U100.96
spi_miso_flash: R225.1, U5.2
spi_mosi: J4.6, U5.5, U100.95
sw_3v3: C205.2, L2.1, U8.11, U8.12
sw_5v0: C201.2, D200.1, L1.1, U7.8
sw_vccint: L3.1, U9.1, U9.2, U9.3
u7_boot: C201.1, U7.1
u7_fb: R200.2, R201.1, U7.4
u8_boot: C205.1, U8.13
u8_comp: R203.1, U8.8
u8_compz: C211.1, R203.2
u8_fb: R204.2, R205.1, U8.7
u8_rt: R202.1, U8.1
u8_ss: C206.1, U8.9
u9_en: R209.2, U9.13
u9_fb: R206.2, R207.1, U9.5
u9_pg: R208.2, U9.4
u9_ss: C214.1, U9.9
uart_rx: J5.2, U100.132
uart_tx: J5.3, U100.133
